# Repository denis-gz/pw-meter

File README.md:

# PW Meter - EMB_1 Graduation Project

## Power Meter - An appliance to measure and log AC power line parameters

The Power Meter can be attached to the AC mains load to measure the following parameters:

 - **AC Voltage** (V, RMS)
 - **AC Current** (A, RMS)
 - **Instantaneous active power** (W)
 - **Instantaneous apparent power** (VA)
 - **Accumulated energy** (Wh)
 - **Power factor** (W/VA ratio)
 - **AC frequency** (Hz)

## Quick Start

In case you have assembled the board using the schematic and components specified in the KiCad project, follow these steps to bring it to life:

1. You may use the supplied firmware image or build your own. No credentials need to be compiled in: Wi-Fi and MQTT settings are entered at runtime (see step 9). If building from source, please verify settings in the `sdkconfig` to match actual hardware. Use usual `idf.py menuconfig` command to re-generate the `sdkconfig`. See also [sdkconfig.defaults](sdkconfig.defaults) file for the minimal set of parameters that differ from ESP-IDF defaults (regenerate it with `idf.py save-defconfig` after changing the configuration).
2. To build the firmware image, use standard **ESP-IDF** tools (CMake, idf.py, etc). Look [here](https://docs.espressif.com/projects/esp-idf/en/v5.5.6/esp32s3/api-guides/build-system.html) for a reference.
3. Flash the firmware via USB Serial/JTAG interface (hold the **BOOT** key while powering on the board). The ESP32's **UART0** interface is also available on the **J3** header for flashing or serial console access (useful for adjusting parameters at runtime).
4. Connect the AC voltage source to the Voltage Transformer module (**U6** sub-board).
5. Pass the **Live** wire of the AC load through the core of the Current Transformer (**SCT013-100** or similar). For low-power loads, wrap the wire around the transformer core several times to amplify the signal. Alternatively, use a sensor with a lower current range. If your sensor includes an internal burden resistor, you may need to desolder the **R3** resistor from the board. Connect the Current Transformer to the **J2** socket. It is also possible to use the PW Meter without a load; in this case, set the `I noise floor` parameter high enough to prevent bogus readings.
6. Connect a **7-30V DC** power source to the **J1** socket. The board itself should not consume more than 5 Watts.
7. The Power Meter starts working immediately, displaying data on the OLED display.
8. Use the **Encoder** to switch pages. Use the Encoder's **push-button** to pause/resume on the Mains page, or to enter the menu on the Settings page. Use a **long press** (> 0.35 sec) to return to the upper level; at the top level, it returns to the Mains page. Use the **RES** key for a hard reset.
9. The Settings page is protected by a 4-digit hex PIN (`0`–`F`): the first four characters of the firmware's ELF SHA256. It is printed at every boot in the console line `I (...) app_init: ELF file SHA256:  53ba1e2f1...` (PIN `53BA` in this example), or can be computed from the build output with `sha256sum build/pw-meter.elf` (`certutil -hashfile build\pw-meter.elf SHA256` on Windows). The PIN changes with every build. Rotate the encoder to choose each digit and press to confirm it. Once unlocked, the settings stay accessible until the display goes to sleep (60 seconds without interaction). The menu covers Wi-Fi credentials, MQTT broker URI, credentials, topic and reporting period, noise floors, calibration coefficients and the energy counter. Text and numeric values are entered in the serial console (**UART0** on **J3**, 921600 baud) when prompted. Settings are stored in NVS and survive reboots.

## Project Structure

### Hardware

The project consists of a main board and two sub-boards:
* **Voltage Transformer:** HW-697 Single-phase AC Active Output Voltage Transformer by LC Technology.
* **Display:** SSD1315 128x64 monochrome I2C OLED (GM009605). Any other SSD1306 I2C compatible display should also work (check the module's address in `idf.py menuconfig`).

Sampling of AC voltage and current channels occur in DMA continuous mode, the rate is 4 kHz per channel, with 12 bit resolution and 12 dB attenuation. The samples are then adjusted for non-linearity using pre-calibrated curves, centered at 0 level, and processed using DSP capabilities of ESP32-S3 chip. Employing hardware acceleration helps keep CPU usage reasonably low (~10% on Core 1, or only 5% without display output).

Please find further details on project's [Schematic](docs/hardware/Schematic_R1.pdf), and PCB board views ([Top Layer](docs/hardware/PcbTop.png), [Inner 1](docs/hardware/PcbInner1.png), [Inner 2](docs/hardware/PcbInner2.png), [Bottom Layer](docs/hardware/PcbBottom.png) and [3D View](docs/hardware/jlcpcb_3d_1.png)).

### Software

The software consists of 6 tasks:

* `reader_task`: ADC sampling task. Performs reading, parsing and adjustment of analog data. Outputs raw values in mV to a ring buffer for the Compute Task.
* `compute_task`: Processes data in 10-cycle chunks. Performs all mathematical calculations and outputs results to the queue for the Interface Task.
* `interface_task`: Applies filtering, updates the OLED display, handles user input from the rotary encoder and console. Sends a copy of the UI data to the Telemetry Task.
* `telemetry_task`: Maintains Wi-Fi and MQTT connections and publishes data to the MQTT broker as JSON, to the `<topic>/metrics/power` and `<topic>/metrics/device` sub-topics.
* `indicator_task`: Drives the status LED (Wi-Fi searching, connected, MQTT transmit and error blinks).
* `console_input_task`: A service task created by the console event loop that handles prompts and waits for user input from the UART console.

The `PowerMeterApp` class represents the main class which initializes all tasks and waits for a stop event. It handles task shutdown, and the `app_main()` function recreates the instance if needed.

## Signal Path

## Data Flow

## Technology

* **MCU:** Espressif ESP32-S3-WROOM-1 N16R2 module
* **AC Voltage Input:** [HW-697](http://www.chinalctech.com/cpzx/Programmer/Sensor_Module/250.html) module by LC Tech (ZMPT101B transformer paired with an LM358 op-amp)
* **AC Current Input:** [SCT013-100](http://en.yhdc.com/comp/file/download.do?id=941) Split-core current transformer (100A, 2000:1 ratio)
* **Display:** GM009605 OLED module based on SSD1306 controller (I2C bus) (or similar)
* **Input:** EC11 rotary encoder
* **Debugging:** BOOT and RESET buttons, UART, and USB Type-C JTAG/Serial ports
* **Software:** ESP-IDF v5.5.6-based CMake project, developed with QtCreator v18.0.2
* **Third-party components:**
    * `nopnop2002/ssd1306`: OLED display support
* **PCB:** 4-layer FR-4 PCB (100x50 mm), developed in KiCad 9.0.7. Mostly uses SMT components (0805 and 0603).

## Example Output

## Author

Copyright © Denys Zavorotnyi, 2026  

## License

[MIT License](LICENSE)

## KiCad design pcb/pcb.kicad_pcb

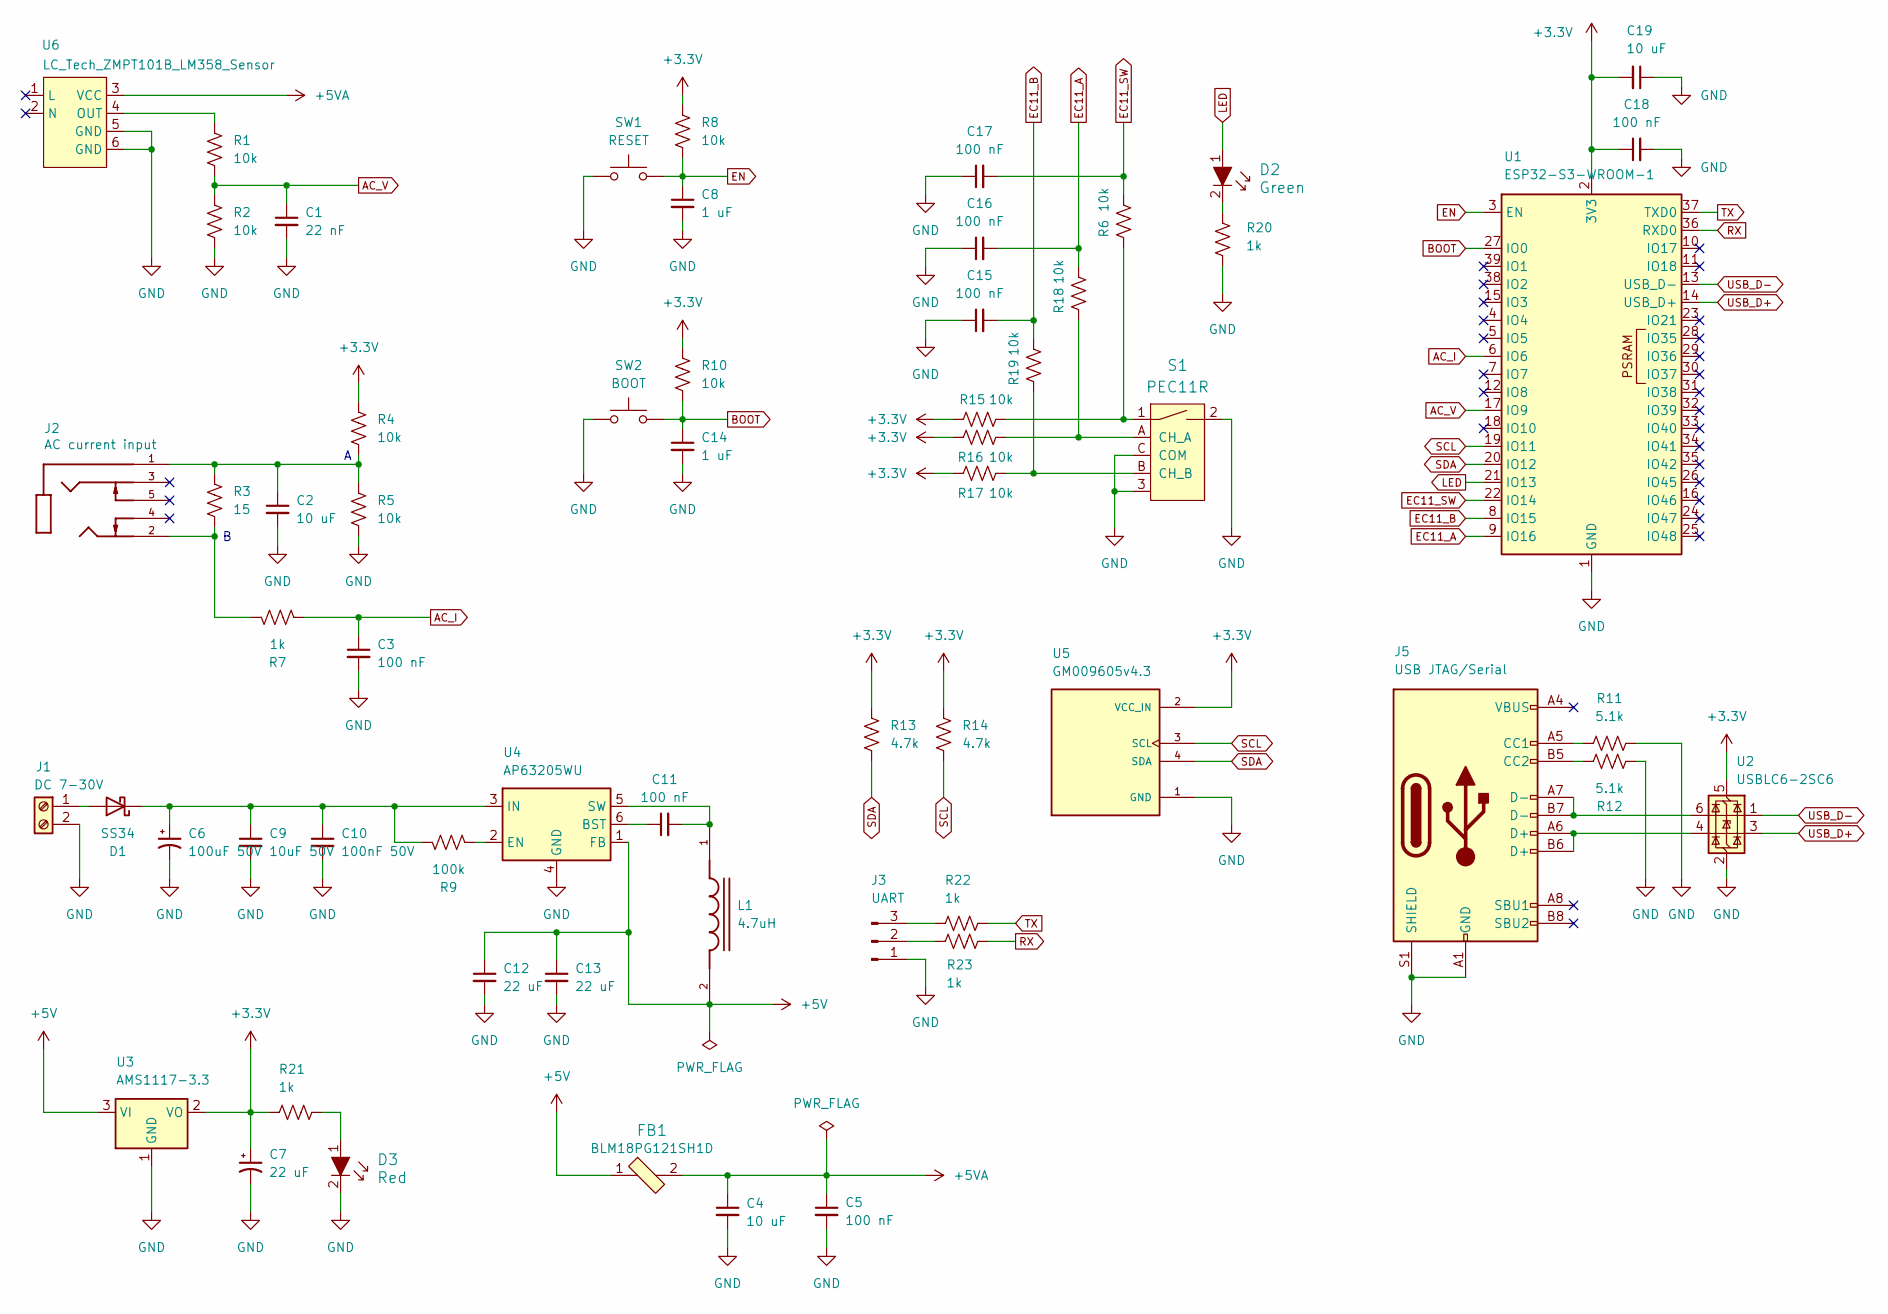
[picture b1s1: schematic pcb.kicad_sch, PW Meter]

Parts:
C1: 22 nF; C_0805_2012Metric; LCSC C1729
C2, C4, C19: 10 uF; C_0805_2012Metric; LCSC C440198
C3, C5, C11, C15, C16, C17, C18: 100 nF; C_0805_2012Metric; LCSC C49678
C6: 100uF 50V; CP_Elec_8x10.5; LCSC C970687
C7: 22 uF; CP_EIA-3528-21_Kemet-B; LCSC C1953099
C8, C14: 1 uF; C_0805_2012Metric; LCSC C28323
C9: 10uF 50V; C_0805_2012Metric; LCSC C440198
C10: 100nF 50V; C_0805_2012Metric; LCSC C49678
C12, C13: 22 uF; C_0805_2012Metric; LCSC C45783
D1: SS34; D_SMA; LCSC C8678
D2: Green; LED_0603_1608Metric; MPN KT-0603G; LCSC C12624
D3: Red; LED_0603_1608Metric; MPN KT-0603R; LCSC C2286
FB1: BLM18PG121SH1D; 0603; MPN BLM18PG121SN1D; Digi-Key_PN 490-1037-1-ND
J1: DC 7-30V; TerminalBlock_Phoenix_MKDS-1,5-2-5.08_1x02_P5.08mm_Horizont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; LCSC C5183929
J2: AC current input; XKB_PJ-325C5-G; PARTREV A0
J3: UART; PinHeader_1x03_P2.54mm_Vertical
J5: USB JTAG/Serial; USB_C_Receptacle_G-Switch_GT-USB-7051x; LCSC C2843970
L1: 4.7uH; L_SXN-SDRH5D28; LCSC C26382
R1, R2, R4, R5, R6, R8, R10, R15, R16, R17, R18, R19: 10k; R_0805_2012Metric; LCSC C17414
R3: 15; R_0805_2012Metric; LCSC C17480
R7: 1k; R_0805_2012Metric; LCSC C17513
R9: 100k; R_0805_2012Metric; LCSC C149504
R11, R12: 5.1k; R_0805_2012Metric; LCSC C27834
R13, R14: 4.7k; R_0805_2012Metric; LCSC C17673
R20, R21, R22, R23: 1k; R_0603_1608Metric; LCSC C21190
S1: PEC11R; Rotary_Encoder_Switched_PEC11R; MPN PEC11R-4215F-S0024; Digi-Key_PN PEC11R-4215F-S0024-ND
SW1: RESET; SW_SPST_B3U-1000P; LCSC C231329
SW2: BOOT; SW_SPST_B3U-1000P; LCSC C231329
U1: ESP32-S3-WROOM-1; LCSC C2913202
U2: USBLC6-2SC6; SOT-23-6; LCSC C7519
U3: AMS1117-3.3; SOT-223-3_TabPin2; LCSC C6186
U4: AP63205WU; TSOT-23-6; LCSC C2071056
U5: GM009605v4.3; MODULE_GM009605v4.3; PARTREV 2018-09-10
U6: LC_Tech_ZMPT101B_LM358_Sensor

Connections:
+3.3V: C7.1, C18.1, C19.2, R4.1, R8.1, R10.1, R13.1, R14.1, R15.1, R16.1, R17.1, R21.1, U1.2 (3V3), U2.5 (VBUS), U3.2 (VO), U5.2 (VCC_IN)
+5V: C12.1, C13.1, FB1.1, L1.2, U3.3 (VI), U4.1 (FB)
+5VA: C4.1, C5.1, FB1.2, U6.3 (VCC)
AC_I: C3.1, R7.2, U1.6 (IO6)
AC_V: C1.1, R1.2, R2.1, U1.17 (IO9)
BOOT: C14.1, R10.2, SW2.2 (B), U1.27 (IO0)
EC11_A: C16.2, R18.2, U1.9 (IO16)
EC11_B: C15.2, R19.2, U1.8 (IO15)
EC11_SW: C17.2, R6.2, U1.22 (IO14)
EN: C8.1, R8.2, SW1.2 (B), U1.3 (EN)
GND: C1.2, C2.2, C3.2, C4.2, C5.2, C6.2, C7.2, C8.2, C9.2, C10.2, C12.2, C13.2, C14.2, C15.1, C16.1, C17.1, C18.2, C19.1, D3.2, J1.2, J3.1, J5.A1 (GND), J5.A12 (GND), J5.B1 (GND), J5.B12 (GND), J5.S1 (SHIELD), R2.2, R5.2, R11.2, R12.1, R20.2, S1.2, S1.3, S1.C (COM), SW1.1 (A), SW2.1 (A), U1.1 (GND), U1.40 (GND), U1.41 (GND), U2.2 (GND), U3.1 (GND), U4.4 (GND), U5.1 (GND), U6.5 (GND), U6.6 (GND)
LED: D2.1, U1.21 (IO13)
unnamed: C2.1, J2.1, R3.1, R4.2, R5.1
unnamed: D1.2 (A), J1.1
unnamed: C6.1, C9.1, C10.1, D1.1 (K), R9.1, U4.3 (IN)
unnamed: D2.2, R20.1
unnamed: D3.1, R21.2
unnamed: J2.2, R3.2, R7.1
unnamed: J3.2, R23.2
unnamed: J3.3, R22.1
unnamed: J5.A5 (CC1), R11.1
unnamed: J5.B5 (CC2), R12.2
unnamed: J5.A6 (D+), J5.B6 (D+), U2.4 (I/O2)
unnamed: J5.A7 (D-), J5.B7 (D-), U2.6 (I/O1)
unnamed: R6.1, R15.2, S1.1
unnamed: R16.2, R18.1, S1.A (CH_A)
unnamed: R17.2, R19.1, S1.B (CH_B)
unnamed: C11.1, U4.6 (BST)
unnamed: R9.2, U4.2 (EN)
unnamed: C11.2, L1.1, U4.5 (SW)
unnamed: R1.1, U6.4 (OUT)
RX: R23.1, U1.36 (RXD0)
SCL: R14.2, U1.19 (IO11), U5.3 (SCL)
SDA: R13.2, U1.20 (IO12), U5.4 (SDA)
TX: R22.2, U1.37 (TXD0)
USB_D+: U1.14 (USB_D+), U2.3 (I/O2)
USB_D-: U1.13 (USB_D-), U2.1 (I/O1)

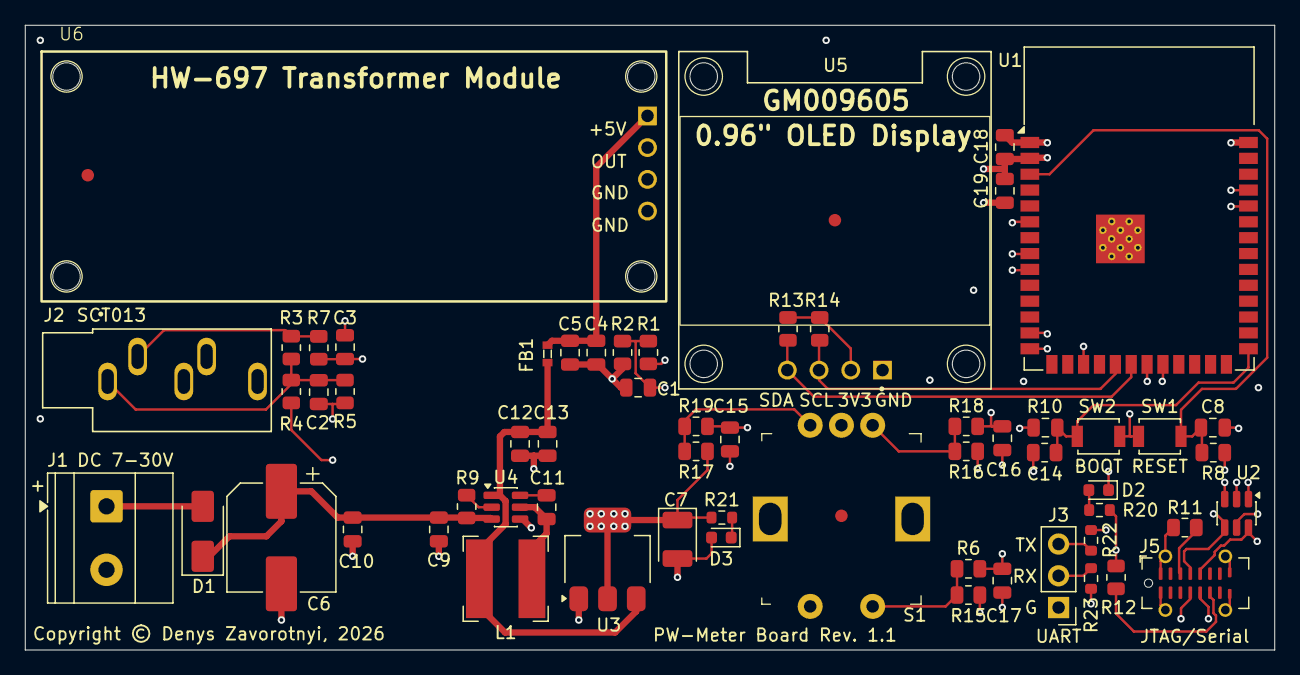
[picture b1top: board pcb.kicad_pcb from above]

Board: 4 copper layers, 100.0 x 50.0 mm, 60 parts (0 on the bottom side), 37 nets.

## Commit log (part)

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2026-04-24 Revision 1
2026-04-25 Work in progress:
    - Fixed V/A alignment logic to have more precise power estimation
    - Fixed SSD1306 and I2C initialization
    - Refactoring
2026-04-26 Version 1.1
    - Added Wi-Fi connectivity
    - Added telemetry task (MQTT reporting)
    - Added Device info, Network info, Log and About pages
    - Added splash screen
    - Fixed button long click
    - Fixed regular frequency spikes
2026-04-28 Implemented console input to allow entering new values of settings
    - Bug fixes and refactoring
2026-04-28 Screenshots added
2026-04-28 Images updated
2026-04-28 Create LICENSE
2026-04-28 Added Data Flow / Signal Path diagrams
2026-04-28 Fixed Wi-Fi settings not being applied
2026-04-29 Bug fixes and refactoring
2026-04-29 Project version updated
2026-06-01 Updated GPIO configuration for production PCB
    - A bit of refactoring
2026-06-01 Improved measurements reporting:
    - Increased voltage display precision to 0.1V
    - Added frequency invalidation on voltages below 5VAC (disconnected/blackout state actually) to avoid bogus readings
2026-06-02 Updated schematic (non-functional)
2026-06-02 Improved parameters stability, esp. AC frequency
    - Added detection of voltage spikes in ADC readings (often caused by OLED interference)
2026-06-02 UI improvements:
    - Status LED logic extended to display following state:
    1. Wi-Fi searching (0.5 sec blinks, permanent mode)
    2. Wi-Fi connection and IP assignment (steady on, permanent mode)
    3. MQTT transmittion (single blink, transient mode)
    4. MQTT error (three blinks, transient mode)
    - System uptime now displays time in Days.Hours:Minutes format (upto 999 days, then invalidates)
2026-06-02 Changed UART0 speed to 921600 bps
2026-06-17 Comments/refactoring
2026-06-17 PCB updated:
    Revision 1.1
    - Corrected footprint of the LC Tech HW-697 module
    - Moved HW-697 signal output track to the In2.Cu layer
    Previous updates:
    - Justified length of the USB D+/D- tracks
2026-06-18 Work in progress:
    - Fixed AC frequency measurement error caused by inaccuracies of ADC clock
    - Fixed reporting of reversed EC11 encoder rotation after replacing it with a better quality part
    - Changed schematic (R1: 10k -> 4.7k) to allow more utilization of available ADC range while
    using lesser level of HW-697 hardware attenuation. This helps prevent AC_V sine wave clipping
    caused by LM358 saturation at 3.5V
    - Temporary switched to a forked esp-idf-ssd1306 repository until my PR is merged to the upstream
2026-06-22 Added display sleep on 1 min encoder input timeout (push to awake)...
    ... - this prevents OLED burnout and reduces ADC noise at the same time
2026-06-22 Added PIN-code protection for Settings:
    - Enter with encoder
    - 4-digits hard-coded
    - Invalidated on screen sleep
2026-06-22 Implemented settings store in NVS memory
2026-06-22 Version 1.3
2026-06-27 README updated
2026-06-30 Fixes/refactoring
2026-06-30 Version 1.4:
    - Refactored Settings menu, fixed bugs, implemented scrolling, added new items:
    - MQTT broker settings (URI, creds, topic, reporting interval)
    - Voltage threshold for energy counter backup to NVS (counter is saved when
    voltage drops below threshold)
    - A menu item to reset energy counter
    - Added MQTT topic to report device status (cpu, memory, uptime)
2026-06-30 Updated schematic version, added copytight
